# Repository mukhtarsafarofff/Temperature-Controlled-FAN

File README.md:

The working principle of this circuit is based on the change of NTC Thermistor's resistance. As the temperature around the module increases, the resistance of the NTC Thermistor decreases, as the temperature around the module decreases, the resistance of the NTC Thermistor increases, and the LM741 Comparator compares the voltage on the potentiometer and the voltage on the Voltage Divider consisting of NTC and Resistor, and when the output is given logic 1, the base of the  Transistor opens and the Fan starts to work . When the output is  logic 0 , the Transistor remains closed because there is no voltage at the base and the Fan turns off .

Das Funktionsprinzip dieser Schaltung basiert auf der Änderung des Widerstands des NTC-Thermistors. Wenn die Temperatur um das Modul herum steigt, nimmt der Widerstand des NTC-Thermistors ab. Wenn die Temperatur um das Modul herum sinkt, steigt der Widerstand des NTC-Thermistors und der Komparator LM741 vergleicht die Spannung am Potentiometer und die Spannung am Spannungsteiler von NTC und Widerstand, und wenn der Ausgang logisch 1 erhält, öffnet sich die Basis des Transistors und der Lüfter beginnt zu arbeiten. Wenn der Ausgang logisch 0 ist, bleibt der Transistor geschlossen, da an der Basis keine Spannung anliegt und der Lüfter abschaltet.

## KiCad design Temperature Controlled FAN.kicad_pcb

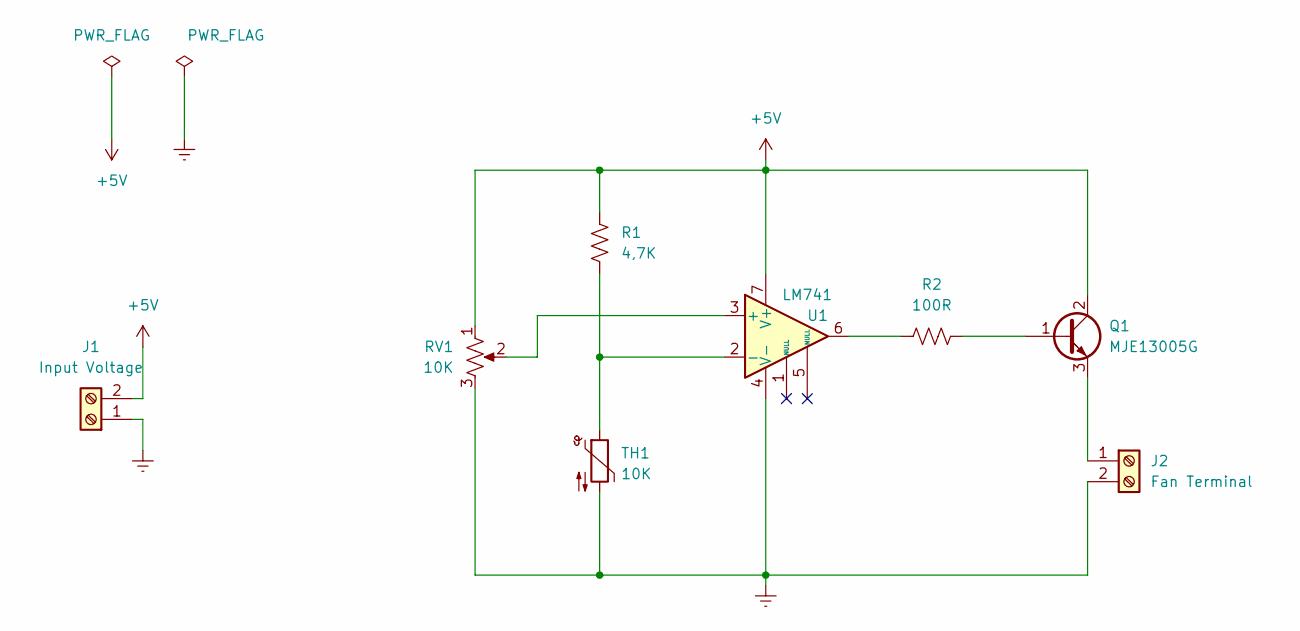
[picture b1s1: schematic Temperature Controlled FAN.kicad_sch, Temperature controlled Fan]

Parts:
J1: Input Voltage; TerminalBlock_bornier-2_P5.08mm
J2: Fan Terminal; TerminalBlock_bornier-2_P5.08mm
Q1: MJE13005G; TO-220-3_Vertical
R1: 4,7K; R_Axial_DIN0411_L9.9mm_D3.6mm_P7.62mm_Vertical
R2: 100R; R_Axial_DIN0411_L9.9mm_D3.6mm_P7.62mm_Vertical
RV1: 10K; Potentiometer_Vishay_148-149_Single_Horizontal
TH1: 10K; R_Radial_Power_L12.0mm_W8.0mm_P5.00mm
U1: LM741; DIP-8_W7.62mm

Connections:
+5V: J1.2, Q1.2 (C), R1.2, RV1.1, U1.7 (V+)
Earth: J1.1, J2.2, RV1.3, TH1.2, U1.4 (V-)
unnamed: J2.1, Q1.3 (E)
unnamed: Q1.1 (B), R2.2
unnamed: R2.1, U1.6
unnamed: RV1.2, U1.3 (+)
unnamed: R1.1, TH1.1, U1.2 (-)

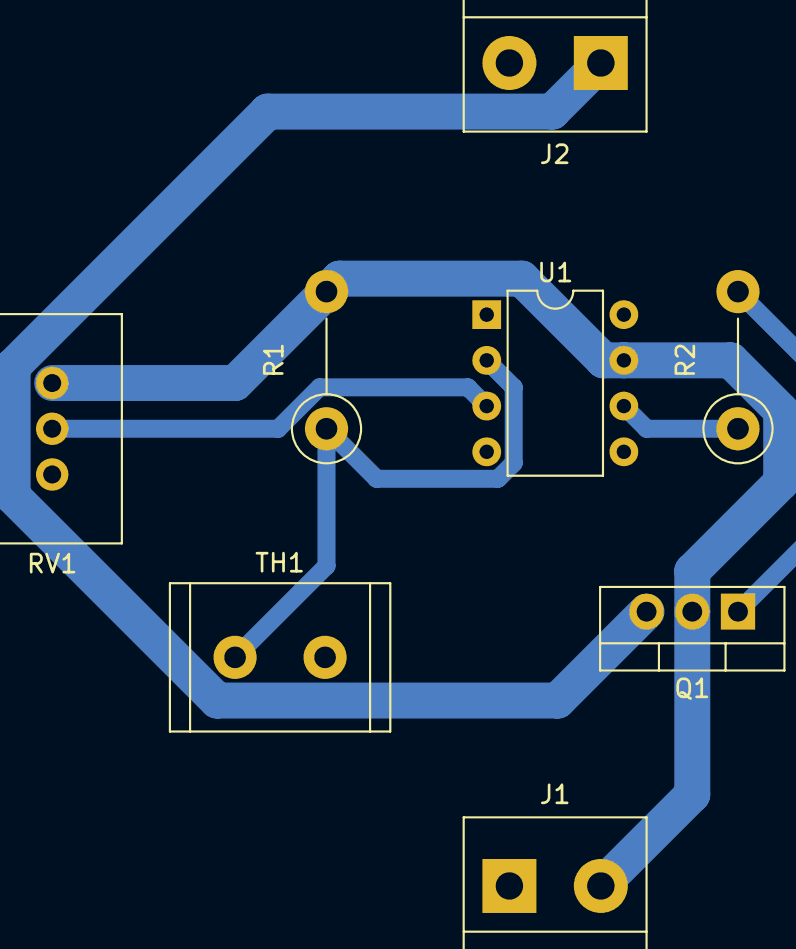
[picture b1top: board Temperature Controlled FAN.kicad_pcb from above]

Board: 2 copper layers, 8 parts (0 on the bottom side), 7 nets.

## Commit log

2024-03-17 LM741 based Temperature Controlled Fan project is accomplished
2024-03-23 Temperature controlled Fan is restored
